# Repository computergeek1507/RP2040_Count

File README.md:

# Copyright and Disclaimer
Copyright: Scott Hanson

This documentation describes Open Hardware and is licensed under the CERN Open Hardware License Version 2 - Strongly Reciprocal. (CERN-OHL-S)

You may redistribute and modify this documentation under the terms of the CERN OHL-S-v2 (https://ohwr.org/cern_ohl_s_v2.txt). This documentation is distributed WITHOUT ANY EXPRESS OR IMPLIED WARRANTY, INCLUDING OF MERCHANTABILITY, SATISFACTORY QUALITY AND FITNESS FOR A PARTICULAR PURPOSE. Please see the CERN OHL v2-S for applicable conditions

**Under CERN OHL-S-v2, derivative work must be publicly released as defined in subsection 3.3**

# SB Pixel Count

SB Pixel Count is a 'pocket' Pixel Counter. The original (V1) board uses a Waveshare RP2040-Tiny Development Board.  All the design files are open source and available on github.

To order PCBs upload the ["GERBER-SB_Pixel_Count.zip"](https://github.com/computergeek1507/SB_Pixel_Count/raw/main/V1/PCB/jlcpcb/production_files/GERBER-SB_Pixel_Count.zip) file in the "V1\PCB\jlcpcb\production_files" folder to jlcpcb.com. Use the "BOM-SB_Pixel_Count.csv" for the JLC Assembly BOM and "CPL-SB_Pixel_Count.csv" as the footprint placement file.

## Assembly

The raw PCB's from JLC will be missing the RP2040-Tiny, OLED, Push Button and PigTails. These parts need to be soldered manually. The case is designed for flat pigtails.

Print the case out of PETG with 0.1mm layer height. Use #2-56 3/8" machine screws for case.

## Board Variants

This repo tracks a few PCB/firmware revisions side by side. `Firmware/SB_Pixel_Count/BoardConfig.h` selects the pin mapping for each via a build flag (`VERSION1`/`VERSION2`/`VERSION3`); the default is `VERSION2`.

| Variant | Folder | MCU module | Firmware | Interactive BOM | Notes |
| --- | --- | --- | --- | --- | --- |
| V1 (Original) | [`V1/`](https://github.com/computergeek1507/SB_Pixel_Count/tree/main/V1) | Waveshare RP2040-Tiny | `VERSION1` | [Open](https://computergeek1507.github.io/SB_Pixel_Count/V1/PCB/bom/ibom.html) | The board described above. |
| V2 | [`V2/`](https://github.com/computergeek1507/SB_Pixel_Count/tree/main/V2) | Seeed XIAO RP2040 | `VERSION2` (default) | [Open](https://computergeek1507.github.io/SB_Pixel_Count/V2/PCB/bom/ibom.html) | Standard redesign around the XIAO RP2040 module - firmware updates over USB (drag-and-drop UF2), no external programmer needed. |
| V2 Lite | [`V2 Lite/`](https://github.com/computergeek1507/SB_Pixel_Count/tree/main/V2%20Lite) | ATtiny1614 (megaTinyCore) | [`Firmware/ATtiny1614_Count/`](https://github.com/computergeek1507/SB_Pixel_Count/tree/main/Firmware/ATtiny1614_Count) | [Open](https://computergeek1507.github.io/SB_Pixel_Count/V2%20Lite/PCB/bom/ibom.html) | Cost-reduced BOM built around a bare ATtiny1614 instead of a RP2040 module; trades USB firmware updates for a UPDI programmer requirement. Uses FAB_LED/SSD1306Ascii instead of the Adafruit libraries to fit in 16KB flash / 2KB RAM. Shares the same case as V2 (`V2/Case/` and `V2 Lite/Case/` are the same design). |
| V3 Pro | [`V3 Pro/`](https://github.com/computergeek1507/SB_Pixel_Count/tree/main/V3%20Pro) | Seeed XIAO RP2040 | `VERSION3` | [Open](https://computergeek1507.github.io/SB_Pixel_Count/V3%20Pro/PCB/bom/ibom.html) | Adds a second button and a microSD card slot for playing back xLights FSEQ sequences on the strip (`Firmware/SB_Pixel_Count/FseqPlayer.*`). |

Each variant folder that has its own `PCB/` directory also has its own `jlcpcb/production_files` gerbers/BOM/CPL for ordering that specific board.

## [Video of SB Pixel Count](https://youtu.be/7ThN9TBFA-g)

## [Part BOM](https://github.com/computergeek1507/SB_Pixel_Count/raw/main/V1/PCB/SB_Pixel_Count_BOM.ods)

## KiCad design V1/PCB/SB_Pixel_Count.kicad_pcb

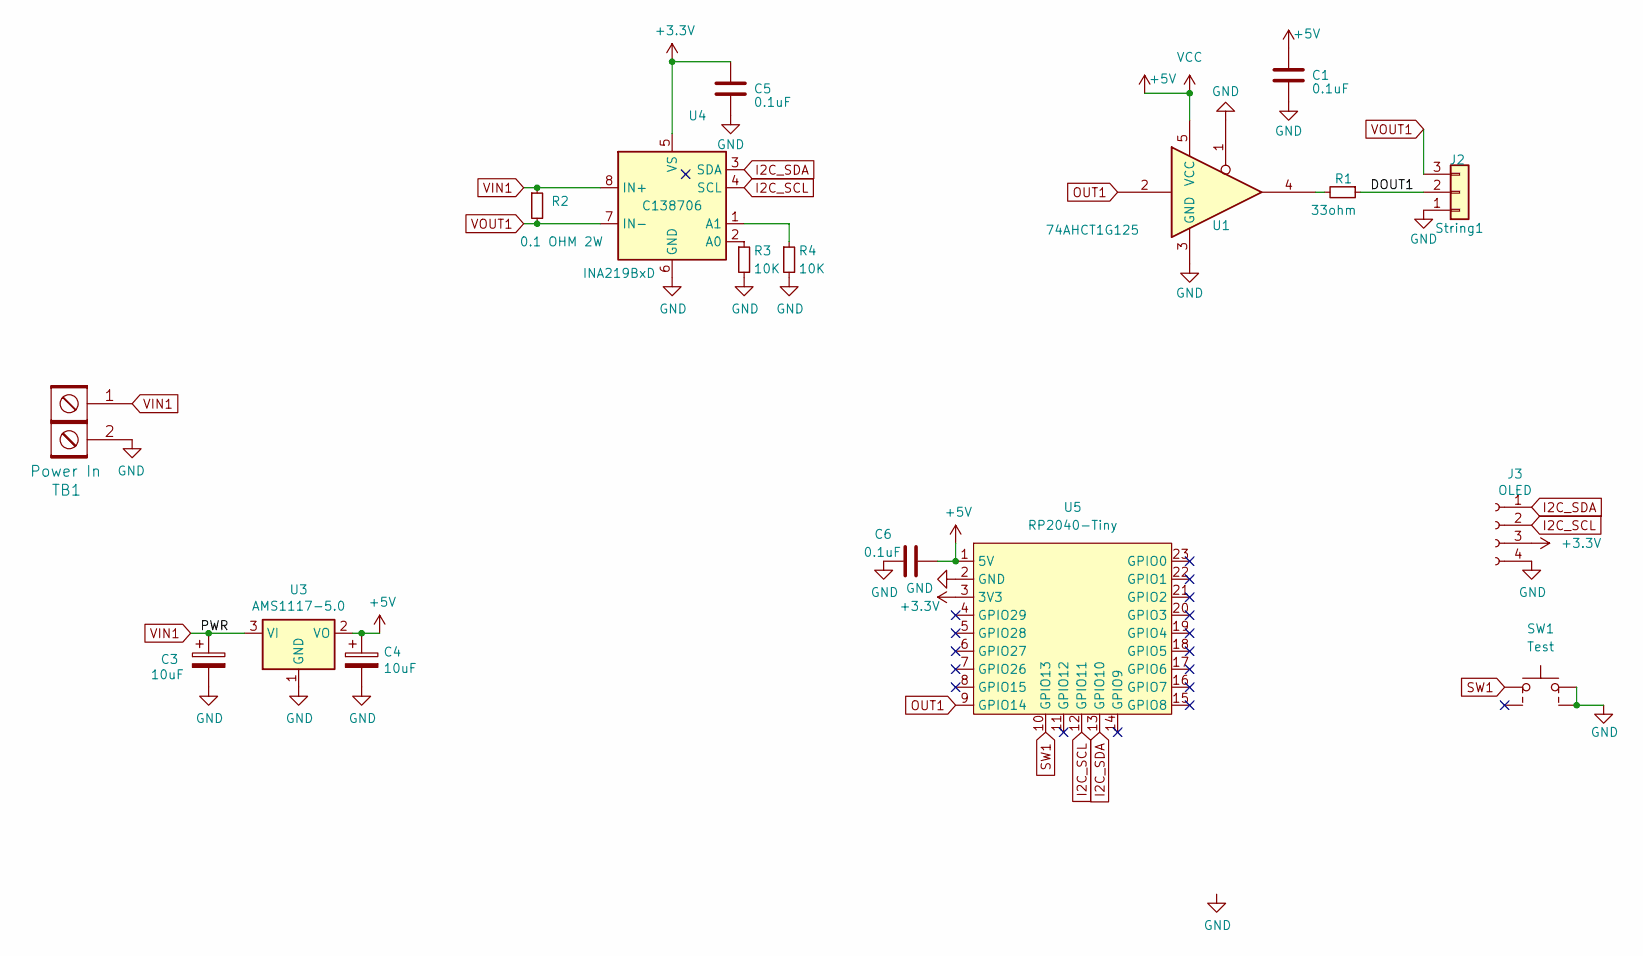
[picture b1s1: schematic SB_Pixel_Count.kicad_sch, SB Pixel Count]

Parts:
C1, C5: 0.1uF; C_0603_1608Metric_Pad1.08x0.95mm_HandSolder; MPN CL10B104KO8NNNC; LCSC C14663
C3, C4: 10uF; C_0805_2012Metric_Pad1.18x1.45mm_HandSolder; MPN GRM21BR61E106KA73L; Digi-Key_PN 490-5523-1-ND
C6: 0.1uF; C_0603_1608Metric_Pad1.08x0.95mm_HandSolder; MPN CL10B104KO8NNNC; Digi-Key_PN 1276-1005-1-ND
J2: String1; PhoenixContact_MCV_3.81mm_3.5mm_1x03_Vertical; MPN 1843619/OSTTJ0311530; Digi-Key_PN 277-5737-ND/ED10555-ND
J3: OLED; OLED-SSD1306-128X64-I2C-THT_SCOTT2; LCSC C225501
R1: 33ohm; R_0603_1608Metric_Pad0.98x0.95mm_HandSolder; MPN RC0603JR-0733RL; LCSC_PN C23140
R2: 0.1 OHM 2W; R_2512_6332Metric_Pad1.40x3.35mm_HandSolder; MPN CSRN2512FTR100; Digi-Key_PN CSRN2512FTR100CT-ND
R3, R4: 10K; R_0603_1608Metric_Pad0.98x0.95mm_HandSolder; MPN RC0603FR-0710KL; Digi-Key_PN 311-10.0KHRCT-ND
SW1: Test; SW_Push_1P1T_NO_6x6mm_H9.5mm; MPN PTS645SL43SMTR92 LFS; LCSC C2834918
TB1: Power In; PhoenixContact_MCV_1,5_2-G-3.81_1x02_P3.81mm_Vertical; MPN 4DB-P108-02; Digi-Key_PN A98472-ND
U1: 74AHCT1G125; TSOP-5_1.65x3.05mm_P0.95mm; MPN 74AHCT1G125W5-7; Digi-Key_PN 74AHCT1G125W5-7DICT-ND
U3: AMS1117-5.0; SOT-223-3_TabPin2; MPN LM1117MPX-50NOPB; LCSC_PN C6187
U4: INA219BxD; SOIC-8_3.9x4.9mm_P1.27mm; MPN INA219BIDR; LCSC C138706
U5: RP2040-Tiny; RP2040-Tiny_Scott

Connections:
+3.3V: C5.1, J3.3, U4.5 (VS), U5.3 (3V3)
+5V: C1.1, C4.1, C6.2, U1.5 (VCC), U3.2 (VO), U5.1 (5V)
/DOUT1: J2.2, R1.1
GND: C1.2, C3.2, C4.2, C5.2, C6.1, J2.1, J3.4, R3.2, R4.2, SW1.2, SW1.4, TB1.2, U1.1, U1.3 (GND), U3.1 (GND), U4.6 (GND), U5.2 (GND)
I2C_SCL: J3.2, U4.4 (SCL), U5.12 (GPIO11)
I2C_SDA: J3.1, U4.3 (SDA), U5.13 (GPIO10)
unnamed: R1.2, U1.4
unnamed: R3.1, U4.2 (A0)
unnamed: R4.1, U4.1 (A1)
OUT1: U1.2, U5.9 (GPIO14)
SW1: SW1.1, U5.10 (GPIO13)
VIN1: C3.1, R2.1, TB1.1, U3.3 (VI), U4.8 (IN+)
VOUT1: J2.3, R2.2, U4.7 (IN-)

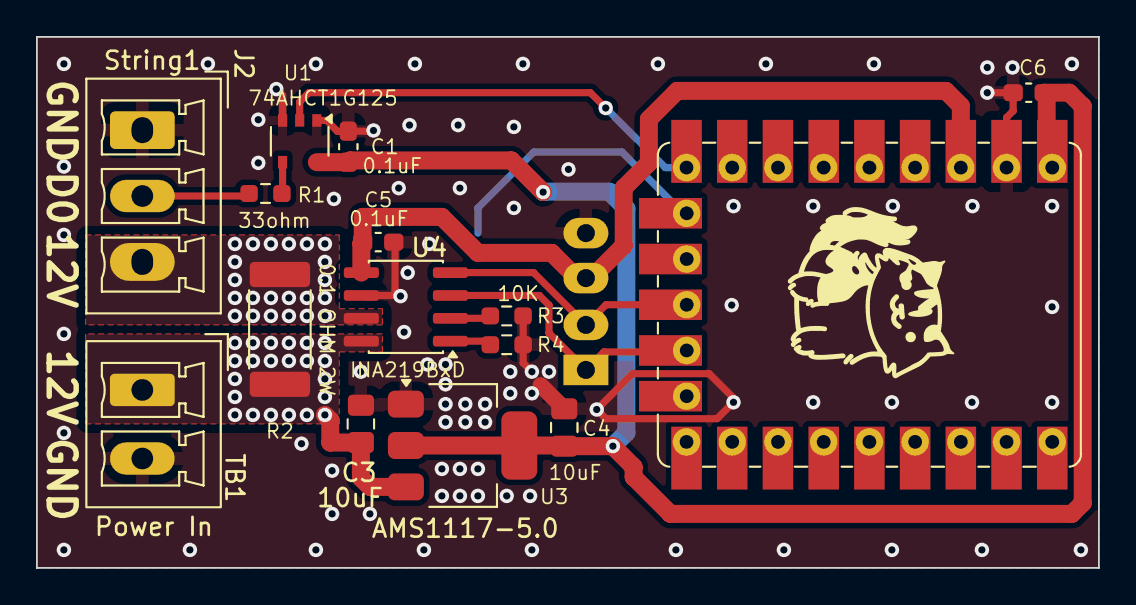
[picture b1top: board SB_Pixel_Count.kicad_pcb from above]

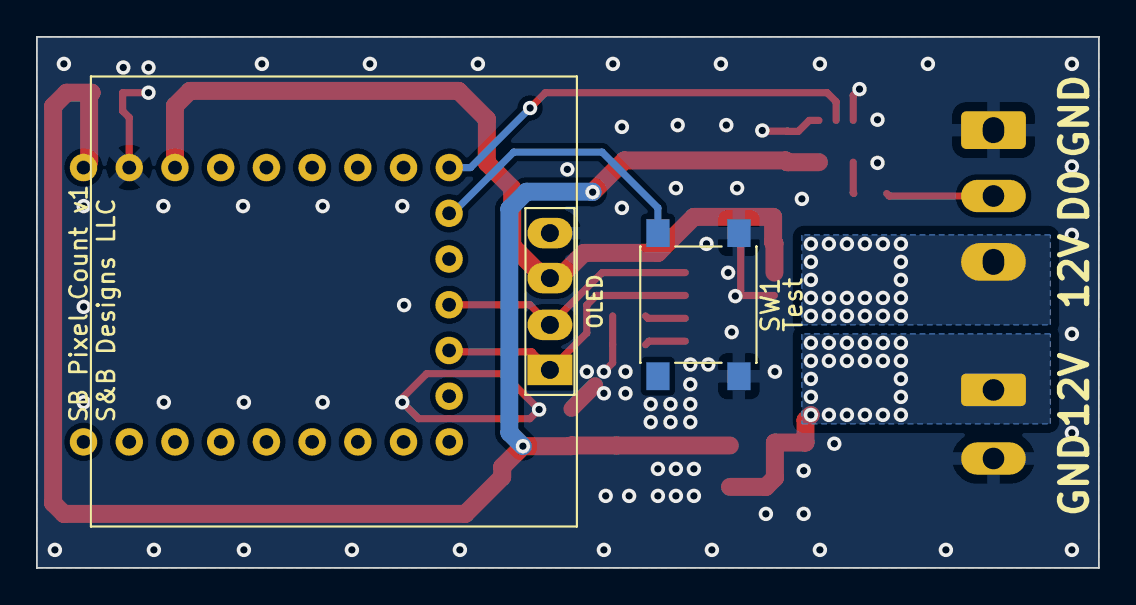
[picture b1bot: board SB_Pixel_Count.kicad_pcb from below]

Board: 2 copper layers, 59.0 x 29.5 mm, 17 parts (2 on the bottom side), 13 nets.

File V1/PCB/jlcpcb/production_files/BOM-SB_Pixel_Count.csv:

Comment,Designator,Footprint,LCSC,Quantity
0.1 OHM 2W,R2,R_2512_6332Metric_Pad1.40x3.35mm_HandSolder,C2903476,1
0.1uF,"C1,C5,C6",C_0603_1608Metric_Pad1.08x0.95mm_HandSolder,C14663,3
10K,"R3,R4",R_0603_1608Metric_Pad0.98x0.95mm_HandSolder,C25804,2
10uF,"C3,C4",C_0805_2012Metric_Pad1.18x1.45mm_HandSolder,C15850,2
33ohm,R1,R_0603_1608Metric_Pad0.98x0.95mm_HandSolder,C23140,1
74AHCT1G125,U1,TSOP-5_1.65x3.05mm_P0.95mm,C7484,1
AMS1117-5.0,U3,SOT-223-3_TabPin2,C6187,1
INA219BxD,U4,SOIC-8_3.9x4.9mm_P1.27mm,C138706,1
Test,SW1,SW_Push_1P1T_NO_6x6mm_H9.5mm,C2834918,1

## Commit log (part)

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2024-03-03 added lies
2024-03-03 fix link
2024-03-03 added more images
2024-03-03 added BOM
2024-03-15 added more notes
2024-05-02 added kibot files
2024-06-29 started V2 software support
2024-06-29 Create compile.yml action
2024-06-29 added RP2040 Zero Version
2024-06-29 working on "V2" ie Seed Studio VIAO rp2040
2024-07-11 working on multiple testing modes and better counting
2024-07-12 new firmware with binary counting
2024-07-12 added v2 case
2025-10-03 rename to v1
2025-10-03 add every 50 mode
2025-10-03 update binary to add every 50 test mode
2025-10-04 add press fit case
2026-02-22 update to 501 leds
2026-03-07 snap case
2026-03-23 add averaging and try three different current levels to pixel testing
